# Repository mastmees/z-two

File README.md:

# z-two
CP/M machine with Z80 emulated on ATMega

See project page at http://www.nomad.ee/micros/z-two/ for full story.

Z-Two runs about 110000 Z80 instructions per second on emulator
running on ATMega1284p, and is fully functional CP/M machine,
albeit a slow one. It uses SD card as storage (maxed out disk
space for CP/M, 16x8MB drives), VGA monitor (80x30 text)
and PS/2 keyboard. There is a serial port with USB-Serial
converter for getting data in and out of the machine.

The emulation code can also be built to run emulated version of
the machine on linux or OSX where the SD card is emulated on a
regular file.

Z80 emulation code was written from scratch, and has features for
debugging and profiling the emulator. It runs all documented Z80
instructions, and enough undocumented ones to pass all 
Frank Cringle's yaze tests (documented flags only).

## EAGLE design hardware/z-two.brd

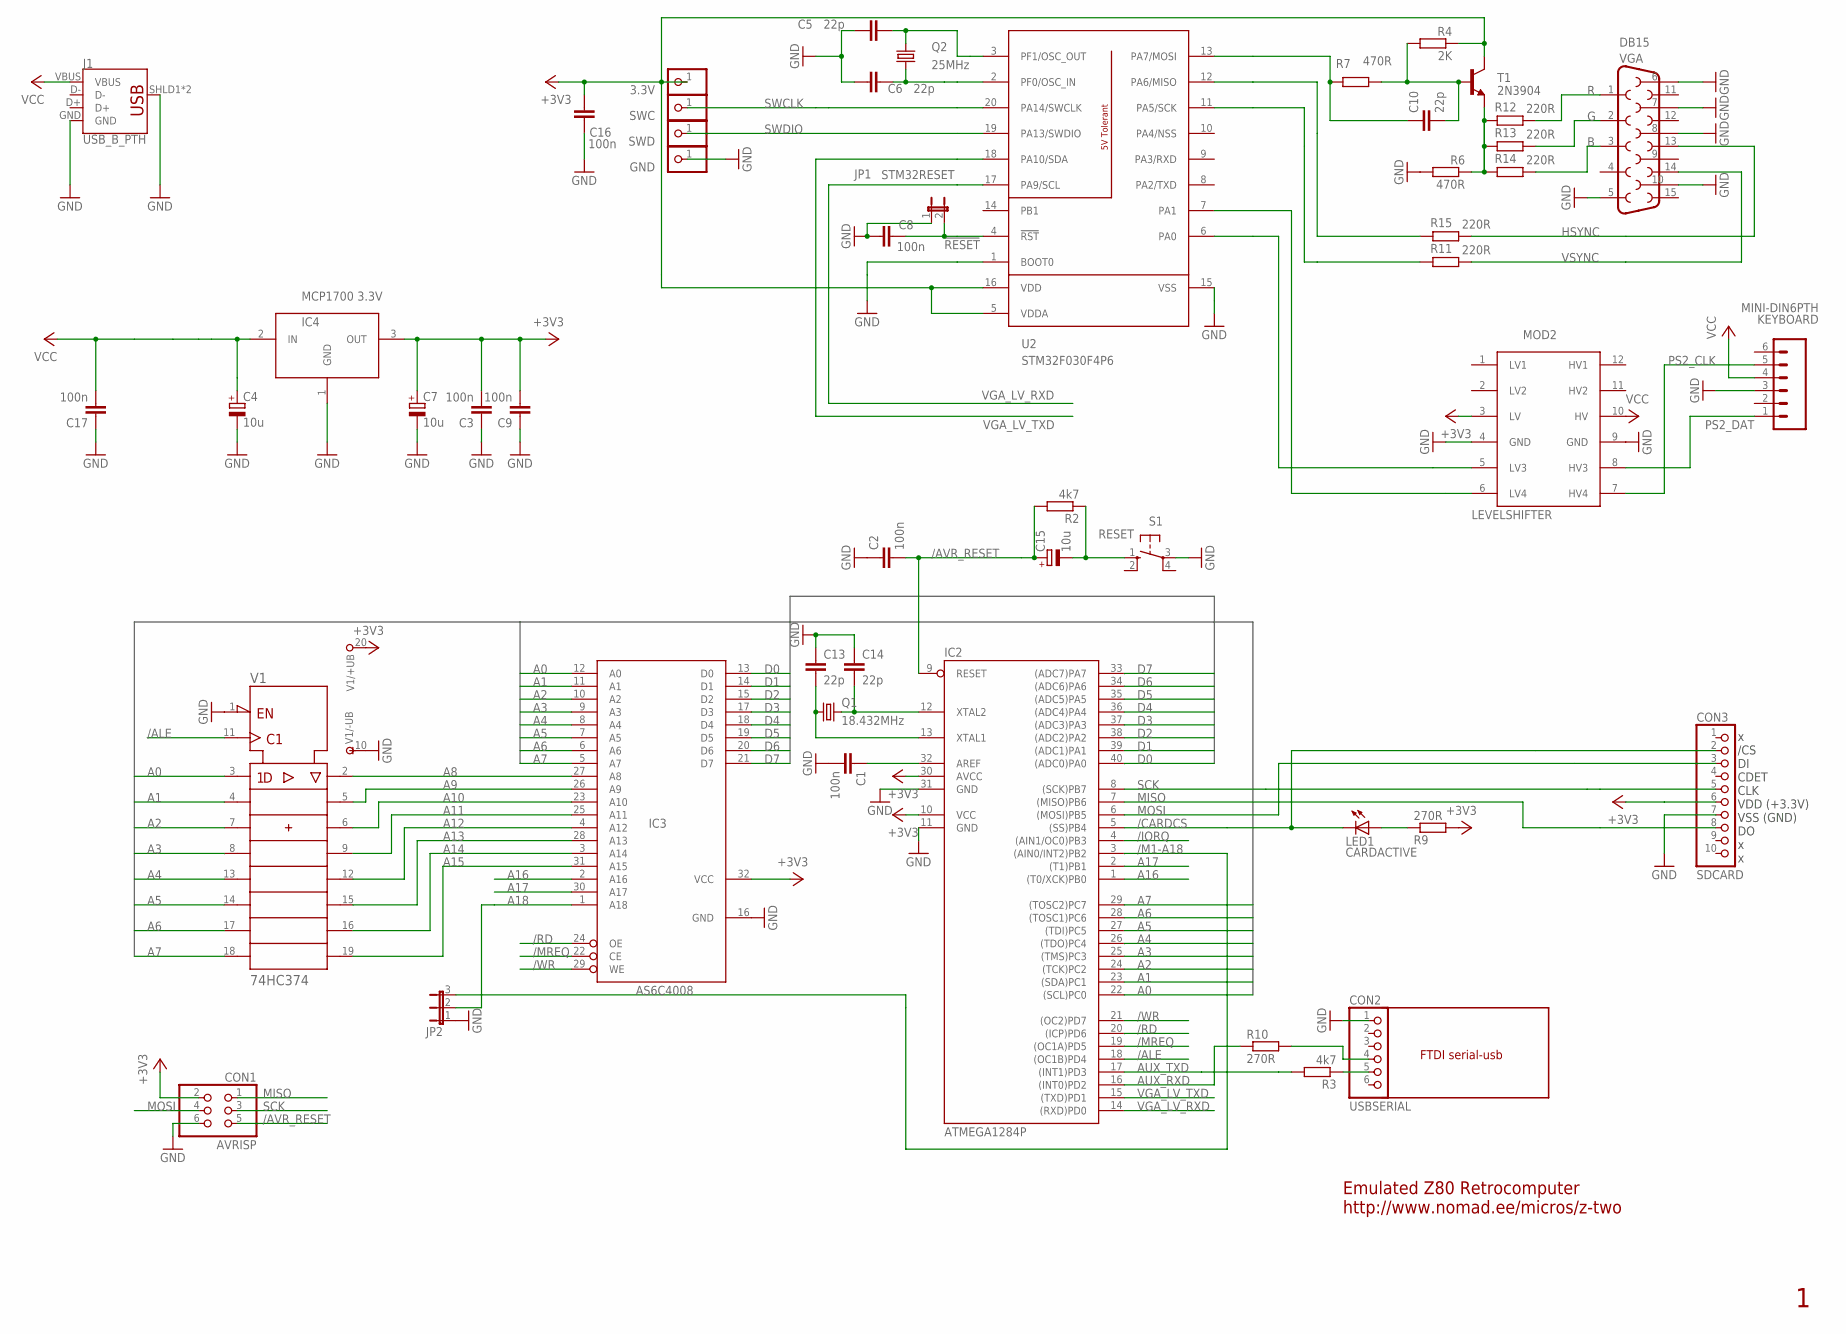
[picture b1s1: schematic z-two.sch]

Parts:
3.3V: PINHD-1X1; 1X01
C1, C2, C3, C8, C9, C16, C17: 100n; C025-025X050; PARTNO 0.1UF, 0603
C4, C7, C15: 10u; E2,5-5
C5, C6, C10: 22p; C025-025X050; PARTNO 22PF, 0603
C13, C14: 22p; C025-025X050; PARTNO 0.1UF, 0603
CON1: AVRISP; 2X03
CON2: USBSERIAL; 1X06
CON3: SDCARD; 1X10
GND: PINHD-1X1; 1X01
IC2: ATMEGA1284P; DIL40
IC3: AS6C4008; DIP32
IC4: MCP1700 3.3V; TO-92
J1: USB_B_PTH; USB-B-PTH
JP1: STM32RESET; 1X02
JP2: JP2E; JP2
KEYBOARD: MINI-DIN6PTH; MINI-DIN6
LED1: CARDACTIVE; LED3MM
MOD2: LEVELSHIFTER; LAVELSHIFTER_N
Q1: 18.432MHz; HC49/S
Q2: 25MHz; HC49/S
R2, R3: 4k7; 0204/7
R4: 2K; 0204/7; PARTNO 2K, 0603
R6, R7: 470R; 0204/7; PARTNO 475R, 0603
R9: 270R; 0204/7; PARTNO 475R, 0603
R10: 270R; 0204/7
R11, R12, R13, R14, R15: 220R; 0204/7
S1: RESET; B3F-10XX
SWC: PINHD-1X1; 1X01
SWD: PINHD-1X1; 1X01
T1: 2N3904; TO92
U2: STM32F030F4P6; MISC-PROCESSOR_TSSOP20
V1: 74HC374; DIL20
VGA: DB15

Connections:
25MHZ: C5.2, Q2.2, U2.3 (PF1/OSC_OUT)
!RESET: C8.1, JP1.2, U2.4 (!RST)
+3V3: 3.3V.1, C3.2, C7.+, C9.2, C16.1, CON1.2, CON3.6, IC2.10 (VCC), IC2.30 (AVCC), IC3.32 (VCC), IC4.3 (OUT), MOD2.3 (LV), R4.1, R9.2, T1.1 (C), U2.5 (VDDA), U2.16 (VDD), V1.20 (+UB)
/ALE: IC2.18 ((OC1B)PD4), V1.11 (CLK)
/AVR_RESET: C2.2, C15.+, CON1.5, IC2.9 (RESET), R2.2
/CARDCS: CON3.2, IC2.5 ((SS)PB4), LED1.K (C)
/IORQ: IC2.4 ((AIN1/OC0)PB3)
/M1-A18: IC2.3 ((AIN0/INT2)PB2), JP2.3
/MREQ: IC2.19 ((OC1A)PD5), IC3.22 (CE)
/RD: IC2.20 ((ICP)PD6), IC3.24 (OE)
/WR: IC2.21 ((OC2)PD7), IC3.29 (WE)
A0: IC2.22 ((SCL)PC0), IC3.12 (A0), V1.3 (1D)
A1: IC2.23 ((SDA)PC1), IC3.11 (A1), V1.4 (2D)
A2: IC2.24 ((TCK)PC2), IC3.10 (A2), V1.7 (3D)
A3: IC2.25 ((TMS)PC3), IC3.9 (A3), V1.8 (4D)
A4: IC2.26 ((TDO)PC4), IC3.8 (A4), V1.13 (5D)
A5: IC2.27 ((TDI)PC5), IC3.7 (A5), V1.14 (6D)
A6: IC2.28 ((TOSC1)PC6), IC3.6 (A6), V1.17 (7D)
A7: IC2.29 ((TOSC2)PC7), IC3.5 (A7), V1.18 (8D)
A8: IC3.27 (A8), V1.2 (1Q)
A9: IC3.26 (A9), V1.5 (2Q)
A10: IC3.23 (A10), V1.6 (3Q)
A11: IC3.25 (A11), V1.9 (4Q)
A12: IC3.4 (A12), V1.12 (5Q)
A13: IC3.28 (A13), V1.15 (6Q)
A14: IC3.3 (A14), V1.16 (7Q)
A15: IC3.31 (A15), V1.19 (8Q)
A16: IC2.1 ((T0/XCK)PB0), IC3.2 (A16)
A17: IC2.2 ((T1)PB1), IC3.30 (A17)
A18: IC3.1 (A18), JP2.2
AUX_RXD: IC2.16 ((INT0)PD2), R10.1
AUX_TXD: IC2.17 ((INT1)PD3), R3.2
B: R14.1, VGA.3
D0: IC2.40 ((ADC0)PA0), IC3.13 (D0)
D1: IC2.39 ((ADC1)PA1), IC3.14 (D1)
D2: IC2.38 ((ADC2)PA2), IC3.15 (D2)
D3: IC2.37 ((ADC3)PA3), IC3.17 (D3)
D4: IC2.36 ((ADC4)PA4), IC3.18 (D4)
D5: IC2.35 ((ADC5)PA5), IC3.19 (D5)
D6: IC2.34 ((ADC6)PA6), IC3.20 (D6)
D7: IC2.33 ((ADC7)PA7), IC3.21 (D7)
G: R13.1, VGA.2
GND: C1.2, C2.1, C3.1, C4.-, C5.1, C6.1, C7.-, C8.2, C9.1, C13.1, C14.1, C16.2, C17.1, CON1.6, CON2.1, CON3.7, GND.1, IC2.11 (GND), IC2.31 (GND), IC3.16 (GND), IC4.1 (GND), J1.GND, J1.SHLD1 (SHIELD), J1.SHLD2 (SHIELD), JP1.1, JP2.1, KEYBOARD.3, MOD2.4 (GND), MOD2.9 (GND), R6.2, S1.3, U2.1 (BOOT0), U2.15 (VSS), V1.1 (!OC), V1.10 (-UB), VGA.5, VGA.6, VGA.7, VGA.8, VGA.10
HSYNC: R15.1, VGA.13
MISO: CON1.1, CON3.8, IC2.7 ((MISO)PB6)
MOSI: CON1.4, CON3.3, IC2.6 ((MOSI)PB5)
unnamed: C6.2, Q2.1, U2.2 (PF0/OSC_IN)
unnamed: R15.2, U2.12 (PA6/MISO)
unnamed: R6.1, R12.2, R13.2, R14.2, T1.3 (E)
unnamed: C14.2, IC2.12 (XTAL2), Q1.2
unnamed: C1.1, IC2.32 (AREF)
unnamed: R11.2, U2.11 (PA5/SCK)
unnamed: MOD2.6 (LV4), U2.7 (PA1)
unnamed: MOD2.5 (LV3), U2.6 (PA0)
unnamed: C10.2, R4.2, R7.1, T1.2 (B)
unnamed: C10.1, R7.2, U2.13 (PA7/MOSI)
unnamed: CON2.5, R3.1
unnamed: C13.2, IC2.13 (XTAL1), Q1.1
unnamed: CON2.4, R10.2
unnamed: C15.-, R2.1, S1.1 (S)
unnamed: LED1.A, R9.1
PS2_CLK: KEYBOARD.5, MOD2.7 (HV4)
PS2_DAT: KEYBOARD.1, MOD2.8 (HV3)
R: R12.1, VGA.1
SCK: CON1.3, CON3.5, IC2.8 ((SCK)PB7)
SWCLK: SWC.1, U2.20 (PA14/SWCLK)
SWDIO: SWD.1, U2.19 (PA13/SWDIO)
VCC: C4.+, C17.2, IC4.2 (IN), J1.VBUS, KEYBOARD.4, MOD2.10 (HV)
VGA_LV_RXD: IC2.14 ((RXD)PD0), U2.17 (PA9/SCL)
VGA_LV_TXD: IC2.15 ((TXD)PD1), U2.18 (PA10/SDA)
VSYNC: R11.1, VGA.14

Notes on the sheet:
FTDI serial-usb
x /CS DI CDET CLK VDD (+3.3V) VSS (GND) DO x x
Emulated Z80 Retrocomputer http://www.nomad.ee/micros/z-two

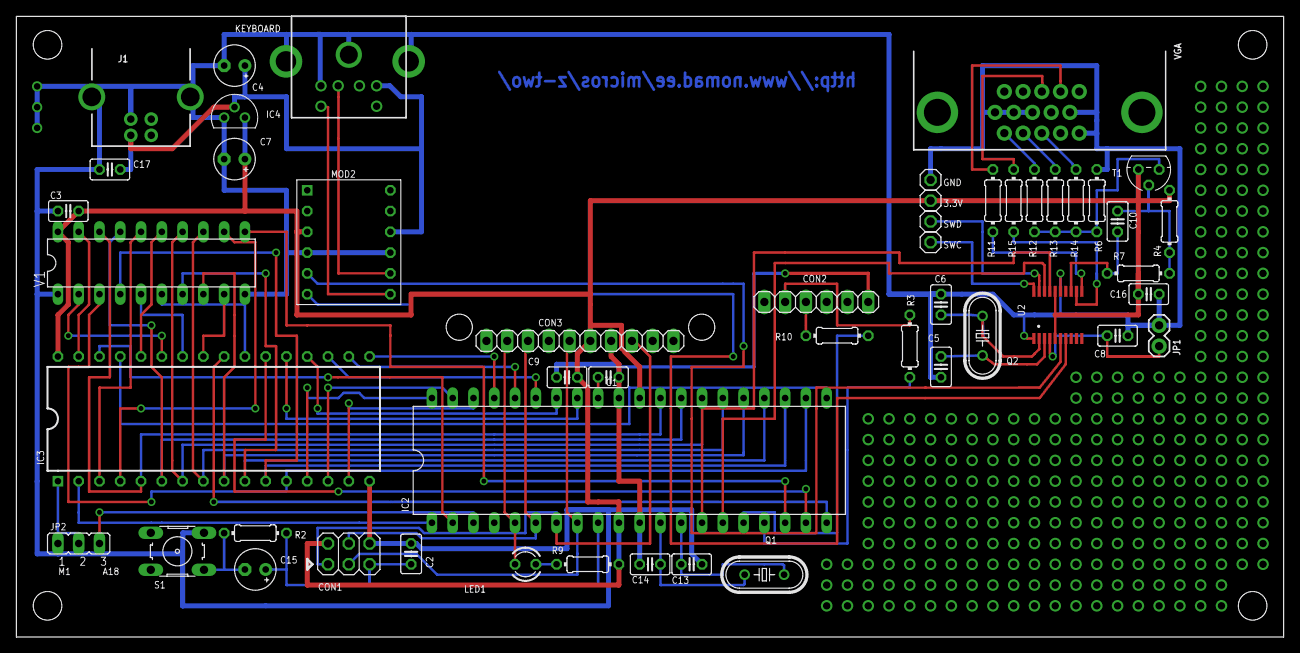
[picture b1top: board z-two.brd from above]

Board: 2 copper layers, 154.9 x 75.9 mm, 50 parts (0 on the bottom side), 70 nets.

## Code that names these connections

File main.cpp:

/* The MIT License (MIT)
 
  Copyright (c) 2018 Madis Kaal <mast@nomad.ee>
 
  Permission is hereby granted, free of charge, to any person obtaining a copy
  of this software and associated documentation files (the "Software"), to deal
  in the Software without restriction, including without limitation the rights
  to use, copy, modify, merge, publish, distribute, sublicense, and/or sell
  copies of the Software, and to permit persons to whom the Software is
  furnished to do so, subject to the following conditions:
 
  The above copyright notice and this permission notice shall be included in all
  copies or substantial portions of the Software.
 
  THE SOFTWARE IS PROVIDED "AS IS", WITHOUT WARRANTY OF ANY KIND, EXPRESS OR
  IMPLIED, INCLUDING BUT NOT LIMITED TO THE WARRANTIES OF MERCHANTABILITY,
  FITNESS FOR A PARTICULAR PURPOSE AND NONINFRINGEMENT. IN NO EVENT SHALL THE
  AUTHORS OR COPYRIGHT HOLDERS BE LIABLE FOR ANY CLAIM, DAMAGES OR OTHER
  LIABILITY, WHETHER IN AN ACTION OF CONTRACT, TORT OR OTHERWISE, ARISING FROM,
  OUT OF OR IN CONNECTION WITH THE SOFTWARE OR THE USE OR OTHER DEALINGS IN THE
  SOFTWARE.
*/


#include <avr/io.h>
#include <avr/interrupt.h>
#include <avr/sleep.h>
#include <avr/wdt.h>
#include <string.h>
#include <avr/pgmspace.h>
#include <util/delay.h>

#include "z80.hpp"
#include "console.hpp"
#include "machine.hpp"
#include "sdcard.hpp"
#include "partitioner.hpp"
#include "aux.hpp"
#include "sdcard.hpp"

SDCard sdcard;
z80 cpu;

ISR(WDT_vect)
{
}

/*
I/O configuration
-----------------
I/O pin                               direction    DDR  PORT
PA0 D0                                input        0    1
PA1 D1                                input        0    1
PA2 D2                                input        0    1
PA3 D3                                input        0    1
PA4 D4                                input        0    1
PA5 D5                                input        0    1
PA6 D6                                input        0    1
PA7 D7                                input        0    1

PB0 A16                               output       1    0
PB1 A17                               output       1    0
PB2 A18                               output       1    0
PB3 /IORQ                             output       1    1
PB4 /SS                               output       1    1
PB5 MOSI                              output       1    1
PB6 MISO                              input        0    1
PB7 SCK                               output       1    1

PC0 A0                                output       1    0
PC1 A1                                output       1    0
PC2 A2                                output       1    0
PC3 A3                                output       1    0
PC4 A4                                output       1    0
PC5 A5                                output       1    0
PC6 A6                                output       1    0
PC7 A7                                output       1    0

PD0 RxD0                              input        0    1
PD1 TxD0                              output       1    1
PD2 RxD1                              input        0    1
PD3 TxD1                              output       1    1
PD4 /ALE                              output       1    1
PD5 /MREQ                             output       1    1
PD6 /RD                               output       1    1
PD7 /WR                               output       1    1
*/
int main(void)
{
  MCUSR=0;
  MCUCR=(1<<JTD); // this does not actually seem to help, fuse needs to be blown too

  // I/O directions and initial state
  DDRA=0x00;
  PORTA=0xff;
  DDRB=0xbf;
  PORTB=0xf8;
  DDRC=0xff;
  PORTC=0x00;
  DDRD=0xfa;
  PORTD=0xff;
  //
  set_sleep_mode(SLEEP_MODE_IDLE);
  sleep_enable();
  // configure watchdog to interrupt&reset, 4 sec timeout
  WDTCSR|=0x18;
  WDTCSR=0xe8;
  // configure timer2 for generic timekeeping, triggering
  // overflow interrupts every 10ms
  TCCR2A=0;
  TCCR2B=7;
  TCNT2=255-180;
  TIMSK2=1;
  sei();
  console.init();
  aux.init();
  console.print("\ec\x0f\e[H\e[2JZ80 emulator for AVR 1.0\r\n");
  sdcard.Init();
  checkdisk();
  copy_bootloader();
  cpu.reset();
  while (1) {
    cpu.step(10000); // running z80 instructions in batches reduces overhead
    wdt_reset();
    WDTCSR|=0x40;
  } 
}

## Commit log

2018-09-01 Publishing project to GitHub
2018-09-01 Updated documents

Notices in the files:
parts and their libraries:
SparkFun-Retired: Licensing: Creative Commons ShareAlike 4.0 International - https://creativecommons.org/licenses/by-sa/4.0
